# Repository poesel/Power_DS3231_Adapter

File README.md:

# Power Adapter
An adapter to switch power with a DS3231 breakout board.

Empty board:

With parts:

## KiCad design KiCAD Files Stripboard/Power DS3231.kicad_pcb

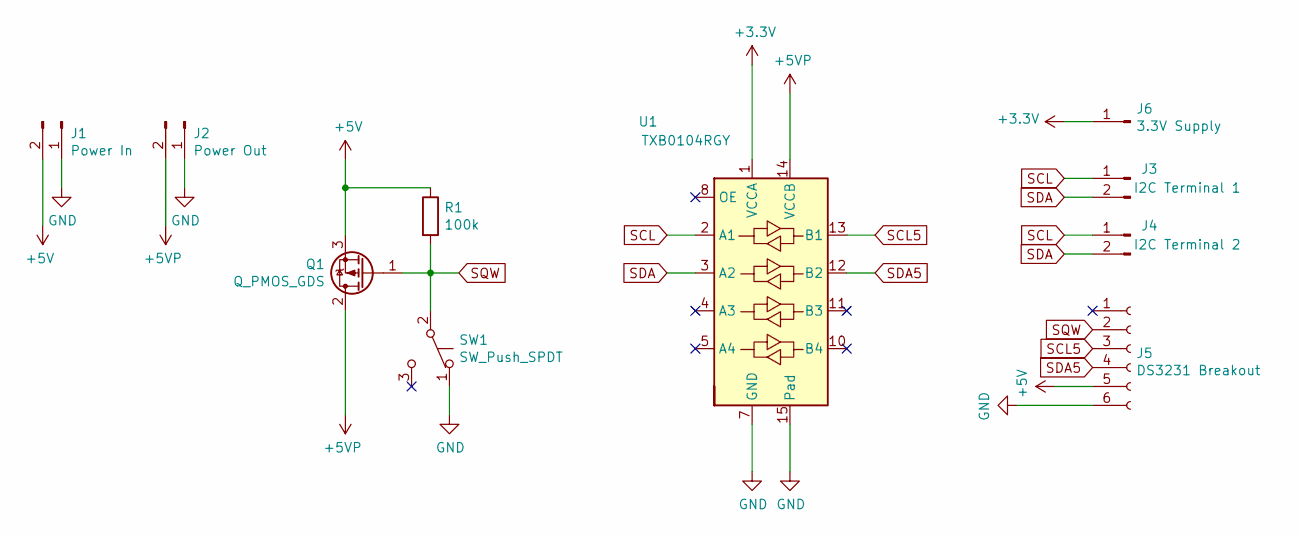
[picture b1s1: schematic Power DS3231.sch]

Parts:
J1: Power In; TerminalBlock_Phoenix_MKDS-3-2-5.08_1x02_P5.08mm_Horizontal
J2: Power Out; TerminalBlock_Phoenix_MKDS-3-2-5.08_1x02_P5.08mm_Horizontal
J3: I2C Terminal 1; PinHeader_1x02_P2.54mm_Vertical
J4: I2C Terminal 2; PinHeader_1x02_P2.54mm_Vertical
J5: DS3231 Breakout; PinSocket_1x06_P2.54mm_Vertical
J6: 3.3V Supply; PinHeader_1x01_P2.54mm_Vertical
Q1: Q_PMOS_GDS; TO-220-3_Vertical
R1: 100k; R_Axial_DIN0207_L6.3mm_D2.5mm_P2.54mm_Vertical
SW1: SW_Push_SPDT; SW_E-Switch_EG1224_SPDT_Angled
U1: TXB0104RGY; Texas_S-PVQFN-N14

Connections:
+3V3: J6.1, U1.1 (VCCA)
+5V: J1.2, J5.5, Q1.3 (S), R1.1
+5VP: J2.2, Q1.2 (D), U1.14 (VCCB)
GND: J1.1, J2.1, J5.6, SW1.1 (A), U1.7 (GND), U1.15 (Pad)
SCL: J3.1, J4.1, U1.2 (A1)
SCL5: J5.3, U1.13 (B1)
SDA: J3.2, J4.2, U1.3 (A2)
SDA5: J5.4, U1.12 (B2)
SQW: J5.2, Q1.1 (G), R1.2, SW1.2 (B)

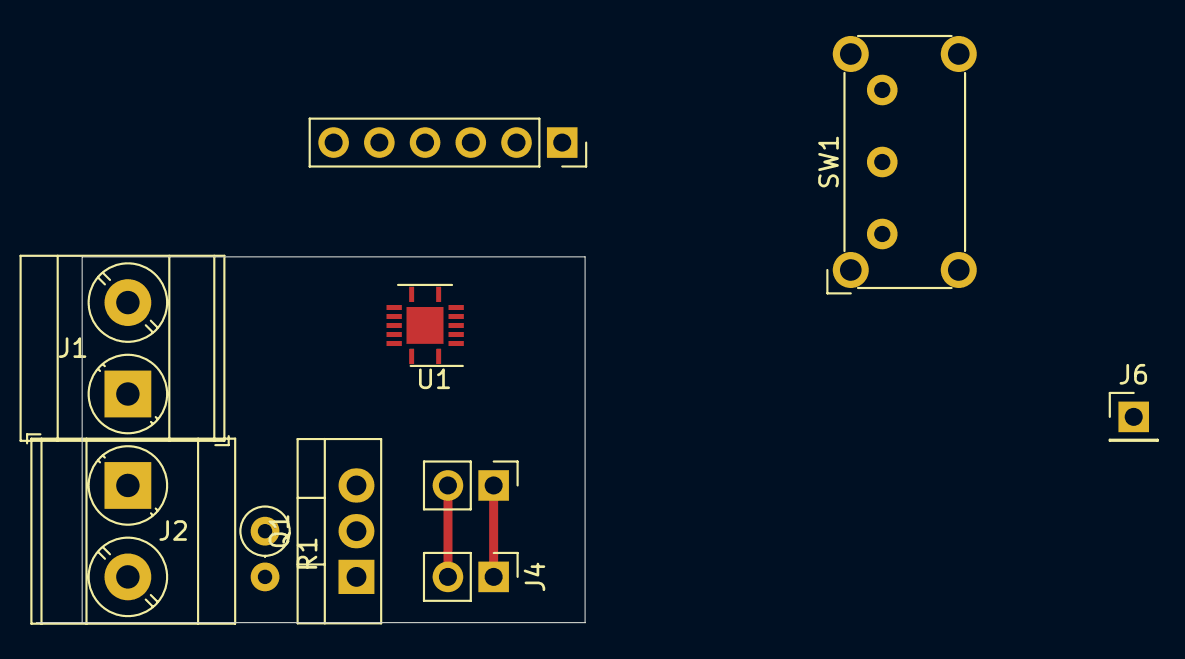
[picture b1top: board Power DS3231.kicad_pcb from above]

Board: 2 copper layers, 30.5 x 20.3 mm, 10 parts (0 on the bottom side), 9 nets.

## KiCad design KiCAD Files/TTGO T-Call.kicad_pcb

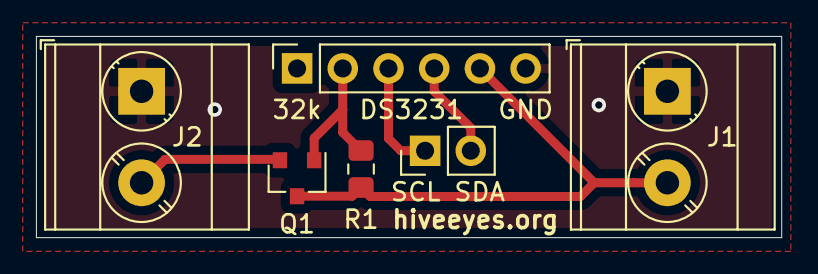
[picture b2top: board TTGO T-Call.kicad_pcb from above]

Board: 2 copper layers, 41.4 x 11.2 mm, 6 parts (0 on the bottom side), 6 nets.

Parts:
J1: Power In; TerminalBlock_Phoenix_MKDS-3-2-5.08_1x02_P5.08mm_Horizontal
J2: Power Out; TerminalBlock_Phoenix_MKDS-3-2-5.08_1x02_P5.08mm_Horizontal
J3: DS3231 Breakout; PinSocket_1x06_P2.54mm_Vertical
J4: I2C Terminal; PinHeader_1x02_P2.54mm_Vertical
Q1: Q_PMOS_GDS; SOT-23
R1: 100k; R_0805_2012Metric_Pad1.15x1.40mm_HandSolder

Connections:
+5V: J1.2, J3.5, Q1.3, R1.1
+5VP: J2.2, Q1.2
GND: J1.1, J2.1, J3.6
SCL: J3.3, J4.1
SDA: J3.4, J4.2
SQW: J3.2, Q1.1, R1.2

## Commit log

2020-05-10 init
2020-06-06 library for DS3231 added several changes to PCB - not finished
2020-06-06 add pictures
2020-06-06 format
2020-06-28 removed debug output
